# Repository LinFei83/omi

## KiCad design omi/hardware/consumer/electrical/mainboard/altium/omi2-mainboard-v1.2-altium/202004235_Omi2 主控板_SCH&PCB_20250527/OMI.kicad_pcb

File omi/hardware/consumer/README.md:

# Omi Consumer — 开源硬件

Omi Consumer 的完整硬件设计文件，全球领先的开源 AI 可穿戴设备。

采用 MIT 许可证（见 [LICENSE](LICENSE)）。

## 目录说明

### 电气（`electrical/`）
- **主板**（nRF5340 + nRF7002）：Altium 源文件、Gerber、原理图（v1.2）
- **充电板**：Altium 源文件、Gerber、原理图（v1.0）
- **FPC（柔性 PCB）**：Altium 源文件、Gerber、原理图（v1.0）

### 物料清单（`bom/`）
- 88 个元器件，含制造商料号（MPN）
- 提供 CSV 与 XLSX 格式

### 机械（`mechanical/`）
- 整机 + 充电器的完整 STEP 装配体
- 按工艺分类的零件：
  - **CNC**：铝外壳（Case A、Case B）、铜质触摸针
  - **注塑**：包覆/外壳（PC+ABS）
  - **硅胶**：内部衬垫（50A/80A 邵氏硬度）
  - **SLA**：框架、导光件、充电器外壳、增强板
- 二维工程图（PDF）

### 装配（`assembly/`）
- 爆炸图照片
- 元器件识别照片
- 带材料标注的参考图

### 包装（`packaging/`）
- 三维 CAD：泡棉内衬、外壳、钣金、完整装配
- 包装图纸与参考照片

## 技术规格

| 部件 | 规格 |
|-----------|---------------|
| 处理器 | nRF5340 双核 Bluetooth LE SoC |
| Wi-Fi | nRF7002 Wi-Fi 6 芯片 |
| 音频 | 2× TDK T5838 顶出音孔 PDM 麦克风 |
| 存储 | CSNP4GCR01 4Gbit NAND Flash |
| IMU | LSM6DS3TR-C 六轴加速度计/陀螺仪 |
| 电池 | 3.7V 150mAh 锂聚合物（定制，D16×H6.1mm） |
| 充电 | BQ25101 锂离子充电 IC、磁吸弹簧针 |
| 马达 | 3V 振动马达（D5.0×H2.5mm） |

## 固件

固件已开源，位于 [`omi/firmware/`](../../firmware/)。基于 Zephyr RTOS 与 nRF Connect SDK 构建。

## 快速上手

1. **制作一台**：用 Gerber 订购 PCB，用 BOM 采购物料，用 STEP 文件加工外壳。
2. **修改设计**：打开 Altium 源文件定制电路，或编辑 STEP 文件重新设计外壳。
3. **烧录固件**：参阅 [固件指南](https://docs.omi.me/doc/developer/firmware/Compile_firmware)。
4. **文档**：访问 [docs.omi.me](https://docs.omi.me/doc/hardware/consumer) 获取详细说明。

## 文件校验和（SHA-256）

克隆后可用下列校验和核对文件完整性。

```
sha256sum -c checksums.sha256
```

### 电气

| 文件 | SHA-256 |
|------|---------|
| `electrical/mainboard/altium/omi2-mainboard-v1.2-altium.zip` | `025c79effcebaa63de9a4adbf59cfb15b5adfe8f3d61d4c21d268320acf5c133` |
| `electrical/mainboard/gerbers/omi2-mainboard-v1.2-gerbers.zip` | `54e126a1aa4e3174eed50e099c7b930646abad261b7f73421ca1526d39dcee49` |
| `electrical/mainboard/gerbers/omi-gerber-files-main-pcb.zip` | `b2c00ffe2e2483daa9871c45a98f38f49896cbc6b4022a4bbbbffe28217259b3` |
| `electrical/mainboard/schematic.pdf` | `0c09fc65f7c191f6d1ec03932042f78a56688b21bb57b9810204640d6e5f527a` |
| `electrical/charger-board/altium/omi2-charger-v1.0-altium.zip` | `7b15cb87102f177e3feaaeaa8315e3f75bd3790b0cf0c68b0caa763b25ac049c` |
| `electrical/charger-board/gerbers/omi2-charger-v1.0-gerbers.zip` | `e7227b24c951c77fd9a1db11d1249fdf2f6db26cf416fa2ef0cf1816f12c4169` |
| `electrical/charger-board/schematic.pdf` | `282e1c469a0cc73f349fbe4fe050f6e1fdc2a86c1dee61c175a50bb6f247a8ad` |
| `electrical/fpc-board/altium/omi2-fpc-v1.0-altium.zip` | `5f30a4a8ef9d21ca5010f039e791a7845486af58db85bce77637518b146a610b` |
| `electrical/fpc-board/gerbers/omi2-fpc-v1.0-gerbers.zip` | `5a8d56466101ef77fd83dc5bd6016d56542443a865142d23864b07aac712ab2b` |
| `electrical/fpc-board/schematic.pdf` | `31d5c900f54dc586440c8d29093e501bde532c45db455b96ac7c552af102919d` |

### 物料清单（BOM）

| 文件 | SHA-256 |
|------|---------|
| `bom/omi-bom.csv` | `01b27487469ddb8ff7b59258959277e3976d6a150b120a643943505c8f892256` |
| `bom/omi-bom.xlsx` | `1445b549f72a37939be9a38401404e8da7ed45a2029204739dac2733b038987b` |
| `bom/omi-bom-original.xlsx` | `a8744d573bc02b62952e164776f72f30ee7929874666da7b452fbc5e8dde6764` |

### 机械

| 文件 | SHA-256 |
|------|---------|
| `mechanical/assemblies/omi-device-charger-assembly.step` | `d7df1b004e159365b69ef57995a21f49e17dbe18d863b359ef611c6f84e473d1` |
| `mechanical/parts/cnc/case-a.step` | `6a23a0693e3d0e0c3068474cb46931f32e7850d6e22266a902060762f165eb1b` |
| `mechanical/parts/cnc/case-b.step` | `ddeba686dd58d06fc5f3b7934e32dd6d720d037b2a4c1828ee44973795fb7a11` |
| `mechanical/parts/cnc/cnc-brass-copper-zinc-polished.zip` | `d19352e101c9c4bb35c6ccba0e71500f06a0023629ec3a303e3cb3ec4a8192bd` |
| `mechanical/parts/cnc/touchpin-1.step` | `8b9941c24fac07849c3b521528be928ec9fcf8f4f7446e2ea78f02263595e4d0` |
| `mechanical/parts/cnc/touchpin-1-v2.step` | `b26275c3c9857e23c46e0ff133d78fd6c8d8b6d4c82b9c0ef77608e720df142a` |
| `mechanical/parts/cnc/touchpin-2.step` | `260945fac51f3c291ced064b37615027997412f226171bc0815a3425d03e4062` |
| `mechanical/parts/cnc/touchpin-2-v2.step` | `7ac7843fc1616f044c74a0b36d6227394d9abb75b93552982b2965906a684471` |
| `mechanical/parts/injection-molding/wrapper.step` | `4a0c2e9494f973fd6e37deea6c30ded2b52af40364d6e357b15f69722eb4cac8` |
| `mechanical/parts/injection-molding/wrapper-drawing.pdf` | `333f625787012c8eb50a4e3f02a31ef9775dd306811b8f620f5891127021413b` |
| `mechanical/parts/silicone/pad.step` | `e47a7ac6076ca5f99ef911499ea609f04d7efe2fb0d346827ed44e172f3f457b` |
| `mechanical/parts/silicone/pad-drawing.pdf` | `714b057e4f0b508212b27c9fcb55bf80e428468fca3fb14ce970fbdf4ac9b815` |
| `mechanical/parts/sla/charger-case-a-ceramic.step` | `9d0fea420fd38bbe7cfb325e5a3b770150ed9efd02239240b8c14abc075f0ebc` |
| `mechanical/parts/sla/charger-case-b-ceramic.step` | `64296a2503a0b70ac032f7f511de47a7274e6af856bb19faef06a2a72104ce67` |
| `mechanical/parts/sla/enhance-plate-black.step` | `e3c0fb9b6a44966e969fc66fe0ce1a2dc0ac410bb00a3932fdfec307d214c7b6` |
| `mechanical/parts/sla/frame-white-translucent.step` | `a0d96a3dcf0e3b7f85885ee5876ddfd58ce187faea3bd3c10ea4a8f5339b0e86` |
| `mechanical/parts/sla/led-guide-white-translucent.step` | `40f1e31e55e18c5f6df762c69b6b705b651f534851b4defb9bf2ef17e5739bfa` |
| `mechanical/parts/sla/pad-ppt-grey.step` | `1df8786beef2a028c1576c3715eb84aef701804750d9ad90eccee1e989fce6ef` |
| `mechanical/parts/sla/touchpin-2-sla-test.step` | `260945fac51f3c291ced064b37615027997412f226171bc0815a3425d03e4062` |
| `mechanical/drawings/omi-2d-drawings.pdf` | `3eb768218947591cea0ae115219fddd1ae40cc9df332d935681289bb778e8861` |
| `mechanical/drawings/manufacturing-specifications.png` | `13ebd6b23de37919f457b96734538ff36be70ec7d6d5f1e94d7a9826393641fb` |

### 包装

| 文件 | SHA-256 |
|------|---------|
| `packaging/cad/packaging-full-assembly.step` | `95298ba059e96c83456d7396db0f50328eaa3931776e65ccbc60e1698b4fa2e4` |
| `packaging/cad/case-packaging.step` | `cd9e71389791b07a10fb84378a1437f069d26292cc4a977ef2fb76296c7ba28d` |
| `packaging/cad/sheet-metal-packaging.step` | `53259fb0dc6f3a382c1ef16fce84c39a410fb7c9486a35b23282382ea4abb1cd` |
| `packaging/cad/foam/foam-assembly.step` | `06ea31b64fc4ab1a18713a98984cb4200caba8c115ee40ff4204a0fe293d8b19` |
| `packaging/cad/foam/foam-bottom.step` | `7c86f3eca98b3a08b582023cf71148322247ecba5e6482e962646e0d80a5bf0d` |
| `packaging/cad/foam/foam-circle.step` | `d0152f117c1f1968c75fb126f8eb92022194266e44e93af73d75c061aaf38f71` |
| `packaging/cad/foam/foam-top.step` | `89df594615bb795ad6e67a9053b61f468d3617c7edee994ee78692c1e632e5fe` |
| `packaging/cad/foam/foam-packaging.step` | `649380aae5dc56b151604301cd7e0c8223e6055c4f8814643e3c49b76fd06c9a` |
| `packaging/cad/foam/foam-drawing.pdf` | `6b1686aa8c1d89c2dc5d511c2abb55b1f456d508b9485d78f037599c10ac2671` |
| `packaging/package-drawing.pdf` | `f9b64171b32a1c432ecd3949f5fc51a28b339b52336c23ef70b2f9e335c173f9` |

### 装配照片

| 文件 | SHA-256 |
|------|---------|
| `assembly/photos/components-disassembled.jpg` | `880e774b49f56a8ec7bf4f4075483f5c0bcf7c0e39962d874d54deb0428b5b71` |
| `assembly/photos/materials-labelled-exploded-view.jpg` | `0cb3e22f08dceaa5cce9c569510985251c2b6c580718ad8d2559987019c2fd00` |
| `assembly/photos/materials-labelled.jpg` | `7857e7b6f7e1686899dd51ec9d11196905ff1f539f09aff08ae2b724904a9555` |
| `assembly/photos/outer-aluminium-covers.jpg` | `0ce99ecfffba3b11a91e754c90c9f4b8c1a14c779b1124cbe6c8b6a69ce71ab1` |

### 包装照片

| 文件 | SHA-256 |
|------|---------|
| `packaging/photos/disassembly-exploded-view.png` | `bfc5a0fa7ed8997aa882cefcff1b7a750578aa6e323e63b720de7ea64d3d54a4` |
| `packaging/photos/package-overview.png` | `2556dd78a18397aa58ed8cb27edd48de5536ce08168a2db371de3e7564f476ad` |
| `packaging/photos/package-render.png` | `2556dd78a18397aa58ed8cb27edd48de5536ce08168a2db371de3e7564f476ad` |
| `packaging/photos/packaging-1.jpg` | `6bf951f71209730e5e031fd28e1e7dc192c86e2b3a5cfdaacd80d8efff77ae38` |
| `packaging/photos/packaging-2.jpg` | `4104233eb7f29c6560d2bfcfbc60bfeea79bc3a1877fb97c0fd19447a350feb1` |
| `packaging/photos/packaging-3.jpg` | `c3ab8314c2465191edaf23849f7da921058b2773add5b372a2891126229362fd` |
| `packaging/photos/packaging-4.jpg` | `6821e45eefc5d4557b88b6282887abebaa9658a7b9f12883f3ca42f4b9e5d2c8` |
| `packaging/photos/packaging-5.jpg` | `f1cd74ab68fbfde7d149bd36ec4f3a5186740af792470c9f2417c561e02404ab` |
| `packaging/photos/packaging-6.jpg` | `a2288a15cb8e9ac8dfc074fed6a6e61a060ff09cecffc6939a92948bfa8dccb5` |
| `packaging/photos/packaging-7.jpg` | `5d0ceae15ed4191c43319c450d89e9a3fcd9ae35db05f605336dd9c8e6d1ca70` |

## 有疑问？

- [GitHub Issues](https://github.com/BasedHardware/omi/issues)：缺陷与功能建议
- [Discord](https://discord.gg/omi)：社区讨论

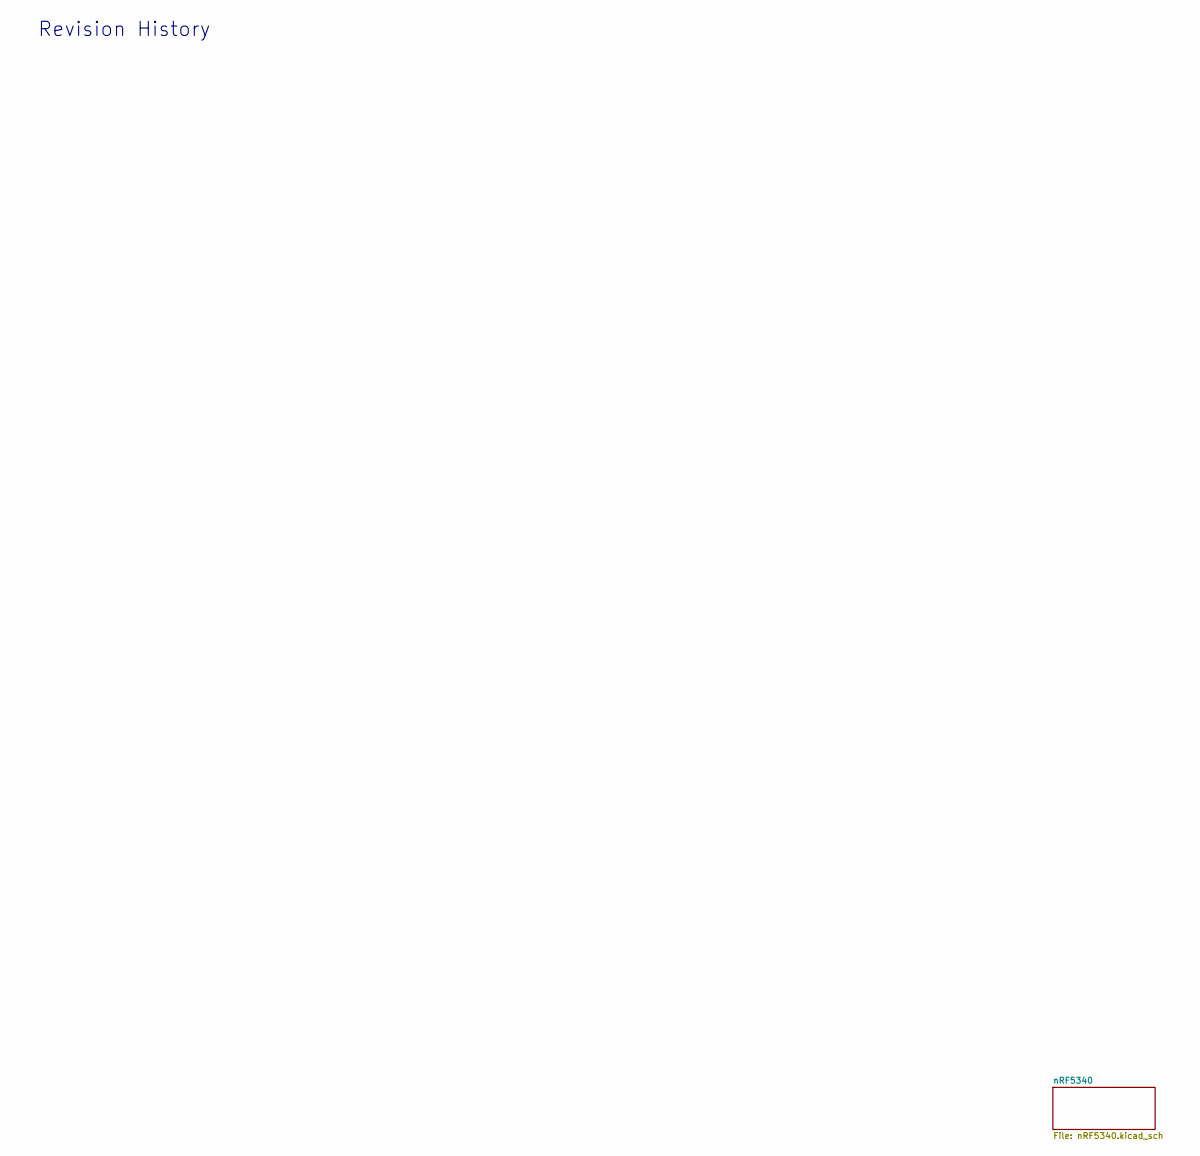
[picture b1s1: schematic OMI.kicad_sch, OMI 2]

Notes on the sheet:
Revision History

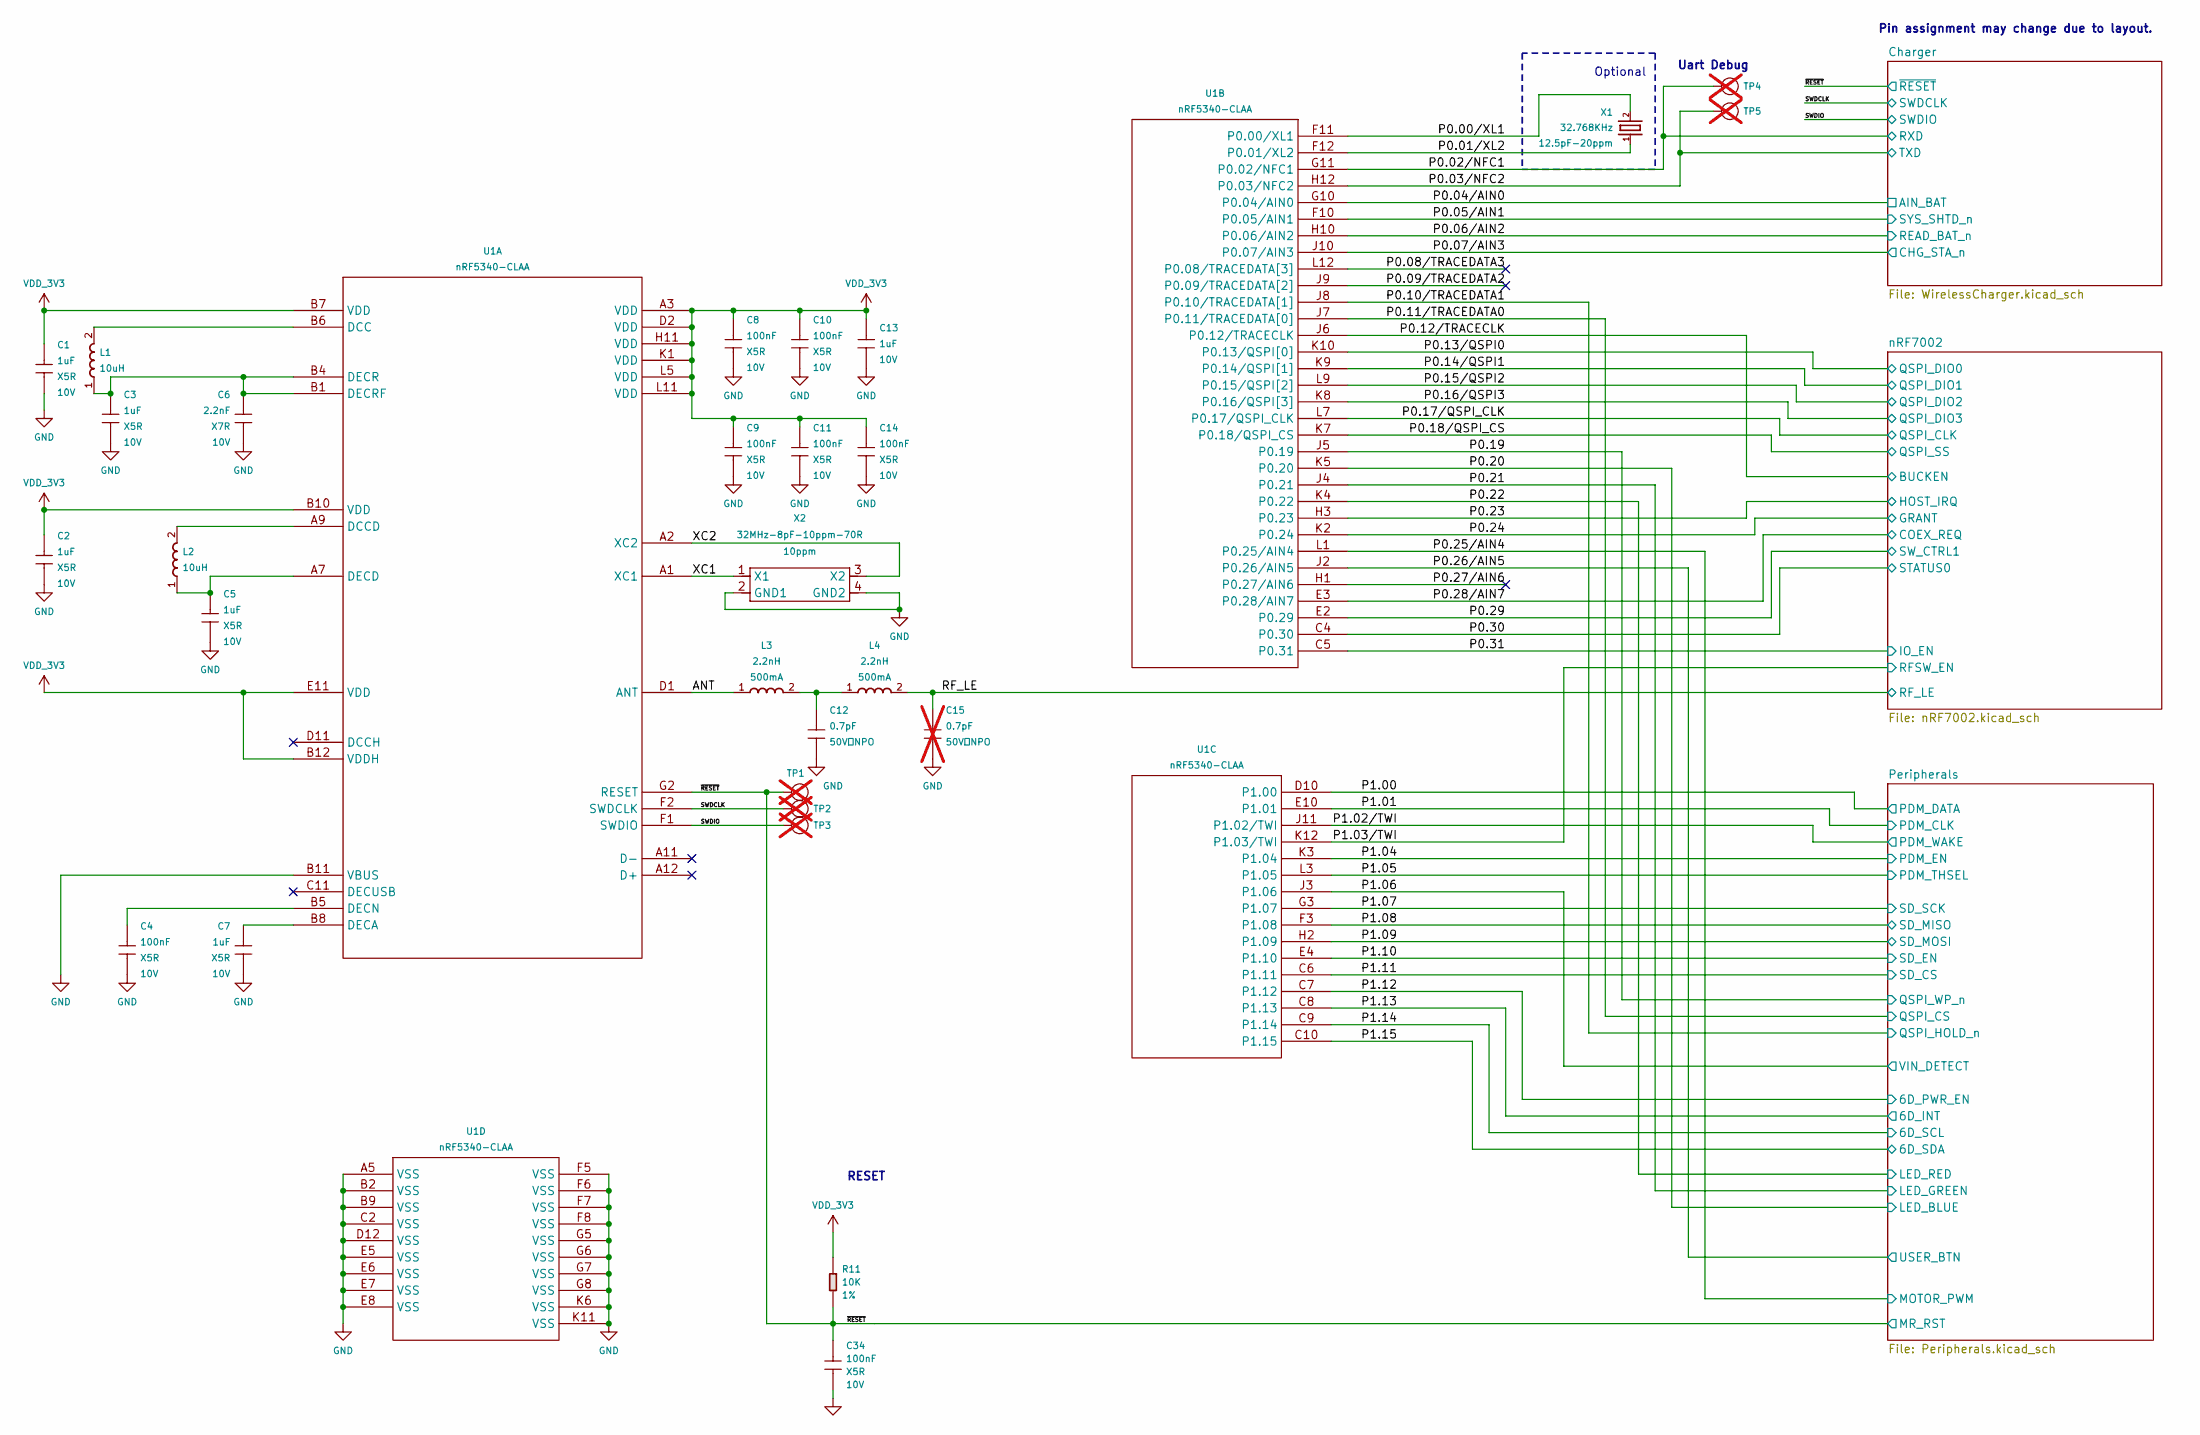
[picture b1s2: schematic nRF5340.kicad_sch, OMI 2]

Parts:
C1, C2, C3, C5, C7, C13: 1uF; C0201; Voltage Rating 10V; MPN GRM033R61A105ME44D
C4, C8, C9, C10, C11, C14, C34: 100nF; C0201; Voltage Rating 10V; MPN CC0201KRX5R6BB104
C6: 2.2nF; C0201; Voltage Rating 10V; MPN CC0201KRX7R6BB222
C12: 0.7pF; C0201; MPN CC0201BRNPO9BNR70
C15: 0.7pF; C0201; MPN CC0201BRNPO9BNR70; not fitted
L1, L2: 10uH; L0603; MPN MWSD1608FE100KT
L3, L4: 2.2nH; L0201; Rating 500mA; MPN CHQ0603T-2N2B-HU
R11: 10K; R0201; Power Rating 1%; MPN RC0201FR-0710KL
TP1, TP2, TP3, TP4, TP5: Test Point; TP-1X0.9MM; Part Type Test Point; not fitted
U1: nRF5340-CLAA; WLCSP94-0.35-4.39X3.994X0.447MM; MPN nRF5340-CLAA
X1: 32.768KHz; X2-SMD-1.6X1.0MM; Rating 12.5pF-20ppm; MPN DST1610A
X2: 32MHz-8pF-10ppm-70R; X4-SMD-1.6X1.2MM; Rating 10ppm; MPN 1S32000049

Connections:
/nRF5340/ANT: L3.1, U1.D1 (ANT)
/nRF5340/P0.00/XL1: U1.F11 (P0.00/XL1), X1.2
/nRF5340/P0.01/XL2: U1.F12 (P0.01/XL2), X1.1
/nRF5340/P0.02/NFC1: TP4.1 (T), U1.G11 (P0.02/NFC1); also elsewhere on the board
/nRF5340/P0.03/NFC2: TP5.1 (T), U1.H12 (P0.03/NFC2); also elsewhere on the board
/nRF5340/P0.04/AIN0: U1.G10 (P0.04/AIN0); also elsewhere on the board
/nRF5340/P0.05/AIN1: U1.F10 (P0.05/AIN1); also elsewhere on the board
/nRF5340/P0.06/AIN2: U1.H10 (P0.06/AIN2); also elsewhere on the board
/nRF5340/P0.07/AIN3: U1.J10 (P0.07/AIN3); also elsewhere on the board
/nRF5340/P0.08/TRACEDATA3: U1.L12 (P0.08/TRACEDATA[3])
/nRF5340/P0.09/TRACEDATA2: U1.J9 (P0.09/TRACEDATA[2])
/nRF5340/P0.10/TRACEDATA1: U1.J8 (P0.10/TRACEDATA[1]); also elsewhere on the board
/nRF5340/P0.11/TRACEDATA0: U1.J7 (P0.11/TRACEDATA[0]); also elsewhere on the board
/nRF5340/P0.12/TRACECLK: U1.J6 (P0.12/TRACECLK); also elsewhere on the board
/nRF5340/P0.13/QSPI0: U1.K10 (P0.13/QSPI[0]); also elsewhere on the board
/nRF5340/P0.14/QSPI1: U1.K9 (P0.14/QSPI[1]); also elsewhere on the board
/nRF5340/P0.15/QSPI2: U1.L9 (P0.15/QSPI[2]); also elsewhere on the board
/nRF5340/P0.16/QSPI3: U1.K8 (P0.16/QSPI[3]); also elsewhere on the board
/nRF5340/P0.17/QSPI_CLK: U1.L7 (P0.17/QSPI_CLK); also elsewhere on the board
/nRF5340/P0.18/QSPI_CS: U1.K7 (P0.18/QSPI_CS); also elsewhere on the board
/nRF5340/P0.19: U1.J5 (P0.19); also elsewhere on the board
/nRF5340/P0.20: U1.K5 (P0.20); also elsewhere on the board
/nRF5340/P0.21: U1.J4 (P0.21); also elsewhere on the board
/nRF5340/P0.22: U1.K4 (P0.22); also elsewhere on the board
/nRF5340/P0.23: U1.H3 (P0.23); also elsewhere on the board
/nRF5340/P0.24: U1.K2 (P0.24); also elsewhere on the board
/nRF5340/P0.25/AIN4: U1.L1 (P0.25/AIN4); also elsewhere on the board
/nRF5340/P0.26/AIN5: U1.J2 (P0.26/AIN5); also elsewhere on the board
/nRF5340/P0.27/AIN6: U1.H1 (P0.27/AIN6)
/nRF5340/P0.28/AIN7: U1.E3 (P0.28/AIN7); also elsewhere on the board
/nRF5340/P0.29: U1.E2 (P0.29); also elsewhere on the board
/nRF5340/P0.30: U1.C4 (P0.30); also elsewhere on the board
/nRF5340/P0.31: U1.C5 (P0.31); also elsewhere on the board
/nRF5340/P1.00: U1.D10 (P1.00); also elsewhere on the board
/nRF5340/P1.01: U1.E10 (P1.01); also elsewhere on the board
/nRF5340/P1.02/TWI: U1.J11 (P1.02/TWI); also elsewhere on the board
/nRF5340/P1.03/TWI: U1.K12 (P1.03/TWI); also elsewhere on the board
/nRF5340/P1.04: U1.K3 (P1.04); also elsewhere on the board
/nRF5340/P1.05: U1.L3 (P1.05); also elsewhere on the board
/nRF5340/P1.06: U1.J3 (P1.06); also elsewhere on the board
/nRF5340/P1.07: U1.G3 (P1.07); also elsewhere on the board
/nRF5340/P1.08: U1.F3 (P1.08); also elsewhere on the board
/nRF5340/P1.09: U1.H2 (P1.09); also elsewhere on the board
/nRF5340/P1.10: U1.E4 (P1.10); also elsewhere on the board
/nRF5340/P1.11: U1.C6 (P1.11); also elsewhere on the board
/nRF5340/P1.12: U1.C7 (P1.12); also elsewhere on the board
/nRF5340/P1.13: U1.C8 (P1.13); also elsewhere on the board
/nRF5340/P1.14: U1.C9 (P1.14); also elsewhere on the board
/nRF5340/P1.15: U1.C10 (P1.15); also elsewhere on the board
/nRF5340/RF_LE: C15.1, L4.2; also elsewhere on the board
/nRF5340/SWDCLK: TP2.1 (T), U1.F2 (SWDCLK); also elsewhere on the board
/nRF5340/SWDIO: TP3.1 (T), U1.F1 (SWDIO); also elsewhere on the board
/nRF5340/XC1: U1.A1 (XC1), X2.1 (X1)
/nRF5340/XC2: U1.A2 (XC2), X2.3 (X2)
/nRF5340/~RESET: C34.1, R11.2, TP1.1 (T), U1.G2 (RESET); also elsewhere on the board
GND: C1.2, C2.2, C3.2, C4.2, C5.2, C6.2, C7.2, C8.2, C9.2, C10.2, C11.2, C12.2, C13.1, C14.2, C15.2, C34.2, U1.A5 (VSS), U1.B2 (VSS), U1.B9 (VSS), U1.B11 (VBUS), U1.C2 (VSS), U1.D12 (VSS), U1.E5 (VSS), U1.E6 (VSS), U1.E7 (VSS), U1.E8 (VSS), U1.F5 (VSS), U1.F6 (VSS), U1.F7 (VSS), U1.F8 (VSS), U1.G5 (VSS), U1.G6 (VSS), U1.G7 (VSS), U1.G8 (VSS), U1.K6 (VSS), U1.K11 (VSS), X2.2 (GND1), X2.4 (GND2); also elsewhere on the board
unnamed: C12.1, L3.2, L4.1
unnamed: L1.2, U1.B6 (DCC)
unnamed: L2.2, U1.A9 (DCCD)
unnamed: C7.1, U1.B8 (DECA)
unnamed: C5.1, L2.1, U1.A7 (DECD)
unnamed: C4.1, U1.B5 (DECN)
unnamed: C3.1, C6.1, L1.1, U1.B1 (DECRF), U1.B4 (DECR)
VDD_3V3: C1.1, C2.1, C8.1, C9.1, C10.1, C11.1, C13.2, C14.1, R11.1, U1.A3 (VDD), U1.B7 (VDD), U1.B10 (VDD), U1.B12 (VDDH), U1.D2 (VDD), U1.E11 (VDD), U1.H11 (VDD), U1.K1 (VDD), U1.L5 (VDD), U1.L11 (VDD); also elsewhere on the board

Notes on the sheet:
Uart Debug
RESET
Pin assignment may change due to layout.
Optional

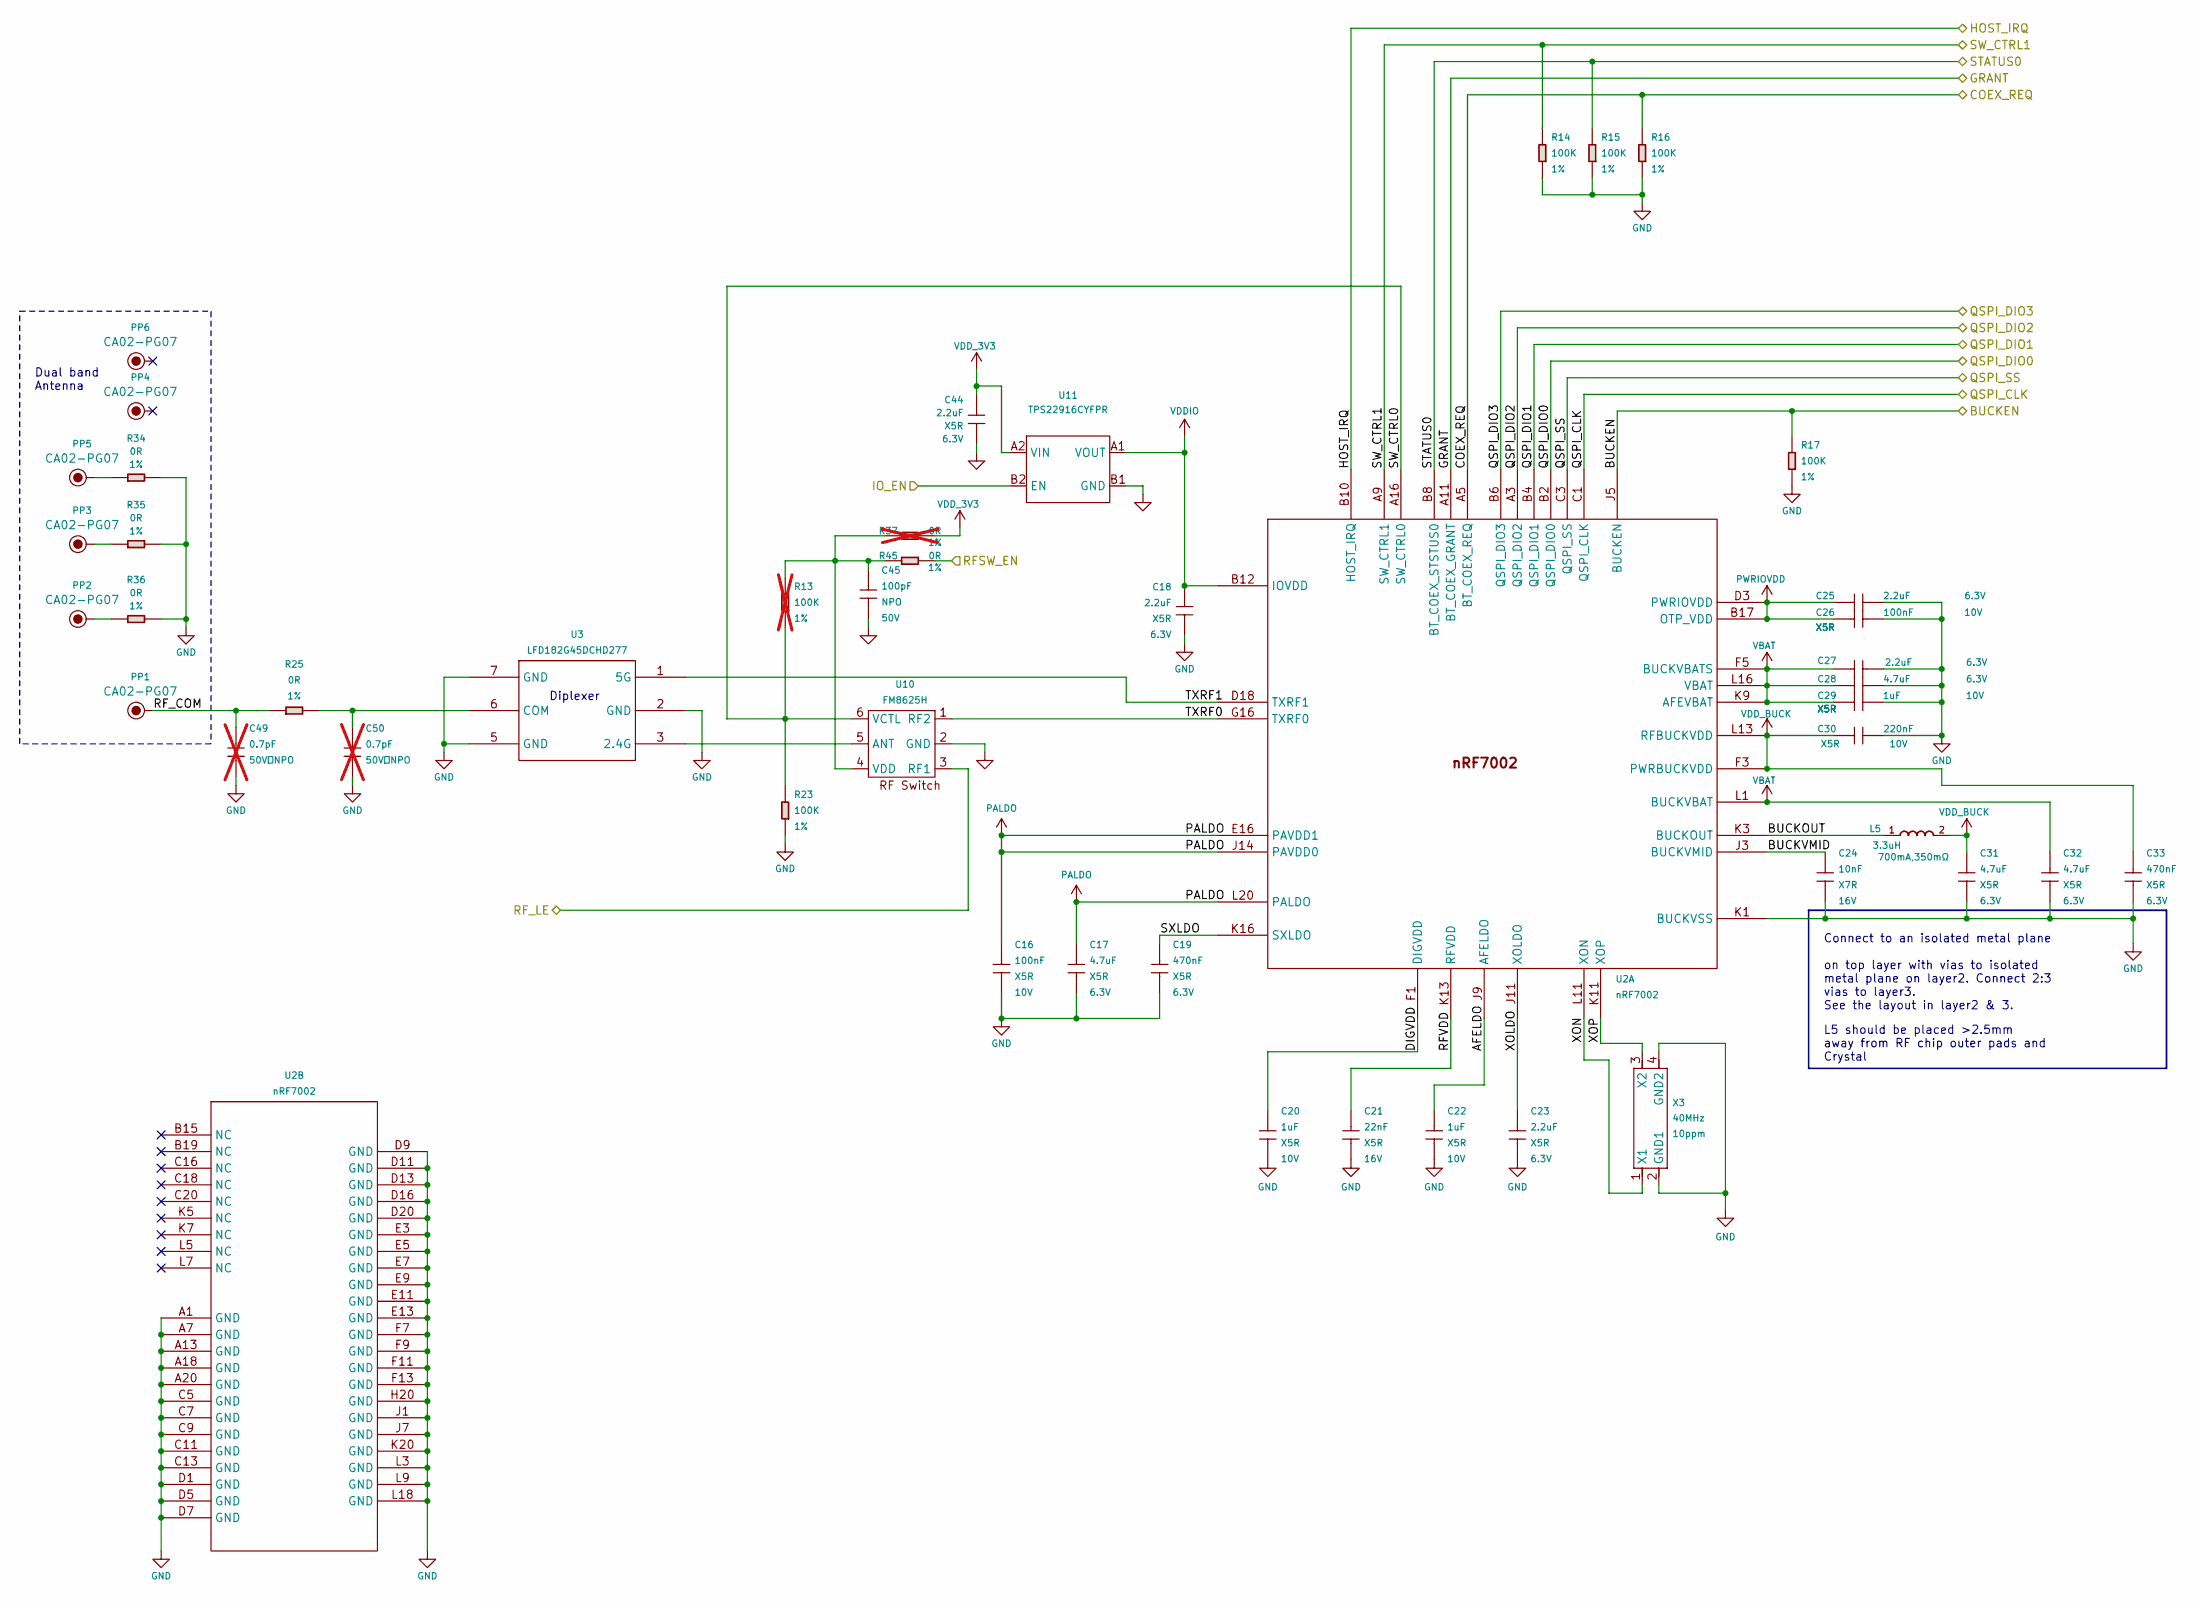
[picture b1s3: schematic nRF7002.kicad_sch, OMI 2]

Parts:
C16, C26: 100nF; C0201; Voltage Rating 10V; MPN CC0201KRX5R6BB104
C17, C28, C31, C32: 4.7uF; C0201; Voltage Rating 6.3V; MPN GRM035R60J475ME15D
C18, C23, C25, C27, C44: 2.2uF; C0201; Voltage Rating 6.3V; MPN 0201X225M6R3NT
C19, C33: 470nF; C0201; Voltage Rating 6.3V; MPN CC0201KRX5R5BB474
C20, C22, C29: 1uF; C0201; Voltage Rating 10V; MPN GRM033R61A105ME44D
C21: 22nF; C0201; Voltage Rating 16V; MPN GRM033R61C223KE84D
C24: 10nF; C0201; Voltage Rating 16V; MPN CC0201KRX7R7BB103
C30: 220nF; C0201; Voltage Rating 10V; MPN CC0201KRX5R6BB224
C45: 100pF; C0201; Voltage Rating 50V; MPN CC0201JRNPO9BN101
C49, C50: 0.7pF; C0201; MPN CC0201BRNPO9BNR70; not fitted
L5: 3.3uH; L0603; Rating 700mA,350mΩ; MPN LQM18PN3R3MFRL
PP1, PP2, PP3, PP4, PP5, PP6: CA02-PG07; POGOPIN-1.4MM-ROUND; MPN CA02-PG07
R13: 100K; R0201; Power Rating 1%; MPN RC0201FR-07100KL; not fitted
R14, R15, R16, R17, R23: 100K; R0201; Power Rating 1%; MPN RC0201FR-07100KL
R25, R34, R35, R36, R45: 0R; R0201; Power Rating 1%; MPN RC0201FR-070RL
R37: 0R; R0201; Power Rating 1%; MPN RC0201FR-070RL; not fitted
U2: nRF7002; nRF7002_WLCSP_R2; MPN nRF7002-CEAA-R7
U3: LFD182G45DCHD277; CAF-50P160X80-6N; MPN LFD182G45DCHD277
U10: FM8625H; DFN6-0.4-1.1X0.7X0.45MM; MPN FM8625H
U11: TPS22916CYFPR; WLCSP4-0.4-0.77X0.77X0.33MM; MPN TPS22916CYFPR
X3: 40MHz; X4-SMD-1.6X1.2MM; Rating 10ppm; MPN CJ17-400001010B20

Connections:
/nRF5340/P0.12/TRACECLK: R17.2, U2.J5 (BUCKEN); also elsewhere on the board
/nRF5340/P0.13/QSPI0: U2.B2 (QSPI_DIO0); also elsewhere on the board
/nRF5340/P0.14/QSPI1: U2.B4 (QSPI_DIO1); also elsewhere on the board
/nRF5340/P0.15/QSPI2: U2.A3 (QSPI_DIO2); also elsewhere on the board
/nRF5340/P0.16/QSPI3: U2.B6 (QSPI_DIO3); also elsewhere on the board
/nRF5340/P0.17/QSPI_CLK: U2.C1 (QSPI_CLK); also elsewhere on the board
/nRF5340/P0.18/QSPI_CS: U2.C3 (QSPI_SS); also elsewhere on the board
/nRF5340/P0.23: U2.B10 (HOST_IRQ); also elsewhere on the board
/nRF5340/P0.24: U2.A11 (BT_COEX_GRANT); also elsewhere on the board
/nRF5340/P0.28/AIN7: R16.2, U2.A5 (BT_COEX_REQ); also elsewhere on the board
/nRF5340/P0.29: R14.2, U2.A9 (SW_CTRL1); also elsewhere on the board
/nRF5340/P0.30: R15.2, U2.B8 (BT_COEX_STSTUS0); also elsewhere on the board
/nRF5340/P0.31: U11.B2 (EN); also elsewhere on the board
/nRF5340/P1.03/TWI: R45.2; also elsewhere on the board
/nRF5340/RF_LE: U10.3 (RF1); also elsewhere on the board
/nRF5340/nRF7002/AFELDO: C22.1, U2.J9 (AFELDO)
/nRF5340/nRF7002/BUCKOUT: L5.1, U2.K3 (BUCKOUT)
/nRF5340/nRF7002/BUCKVMID: C24.1, U2.J3 (BUCKVMID)
/nRF5340/nRF7002/DIGVDD: C20.2, U2.F1 (DIGVDD)
/nRF5340/nRF7002/RFVDD: C21.1, U2.K13 (RFVDD)
/nRF5340/nRF7002/RF_COM: C49.1, PP1.1 (T), R25.1
/nRF5340/nRF7002/SW_CTRL0: R13.1, R23.2, U2.A16 (SW_CTRL0), U10.6 (VCTL)
/nRF5340/nRF7002/SXLDO: C19.1, U2.K16 (SXLDO)
/nRF5340/nRF7002/TXRF0: U2.G16 (TXRF0), U10.1 (RF2)
/nRF5340/nRF7002/TXRF1: U2.D18 (TXRF1), U3.1 (5G)
/nRF5340/nRF7002/XOLDO: C23.1, U2.J11 (XOLDO)
/nRF5340/nRF7002/XON: U2.L11 (XON), X3.1 (X1)
/nRF5340/nRF7002/XOP: U2.K11 (XOP), X3.3 (X2)
GND: C16.2, C17.2, C18.2, C19.2, C20.1, C21.2, C22.2, C23.2, C24.2, C25.2, C26.2, C27.2, C28.2, C29.2, C30.2, C31.2, C32.2, C33.2, C44.1, C45.2, C49.2, C50.2, R14.1, R15.1, R16.1, R17.1, R23.1, R34.2, R35.2, R36.2, U2.A1 (GND), U2.A7 (GND), U2.A13 (GND), U2.A18 (GND), U2.A20 (GND), U2.C5 (GND), U2.C7 (GND), U2.C9 (GND), U2.C11 (GND), U2.C13 (GND), U2.D1 (GND), U2.D5 (GND), U2.D7 (GND), U2.D9 (GND), U2.D11 (GND), U2.D13 (GND), U2.D16 (GND), U2.D20 (GND), U2.E3 (GND), U2.E5 (GND), U2.E7 (GND), U2.E9 (GND), U2.E11 (GND), U2.E13 (GND), U2.F7 (GND), U2.F9 (GND), U2.F11 (GND), U2.F13 (GND), U2.H20 (GND), U2.J1 (GND), U2.J7 (GND), U2.K1 (BUCKVSS), U2.K20 (GND), U2.L3 (GND), U2.L9 (GND), U2.L18 (GND), U3.2 (GND), U3.5 (GND), U3.7 (GND), U10.2 (GND), U11.B1 (GND), X3.2 (GND1), X3.4 (GND2); also elsewhere on the board
unnamed: PP2.1 (T), R36.1
unnamed: PP3.1 (T), R35.1
unnamed: PP5.1 (T), R34.1
unnamed: C50.1, R25.2, U3.6 (COM)
unnamed: U3.3 (2.4G), U10.5 (ANT)
unnamed: C45.1, R13.2, R37.1, R45.1, U10.4 (VDD)
PALDO: C16.1, C17.1, U2.E16 (PAVDD1), U2.J14 (PAVDD0), U2.L20 (PALDO)
PWRIOVDD: C25.1, C26.1, U2.B17 (OTP_VDD), U2.D3 (PWRIOVDD)
VBAT: C27.1, C28.1, C29.1, C32.1, U2.F5 (BUCKVBATS), U2.K9 (AFEVBAT), U2.L1 (BUCKVBAT), U2.L16 (VBAT); also elsewhere on the board
VDDIO: C18.1, U2.B12 (IOVDD), U11.A1 (VOUT)
VDD_3V3: C44.2, R37.2, U11.A2 (VIN); also elsewhere on the board
VDD_BUCK: C30.1, C31.1, C33.1, L5.2, U2.F3 (PWRBUCKVDD), U2.L13 (RFBUCKVDD)

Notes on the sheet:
Diplexer
Connect to an isolated metal plane on top layer with vias to isolated metal plane on layer2. Connect 2:3 vias to layer3. See the layout in layer2 & 3.
L5 should be placed >2.5mm away from RF chip outer pads and Crystal
Dual band Antenna

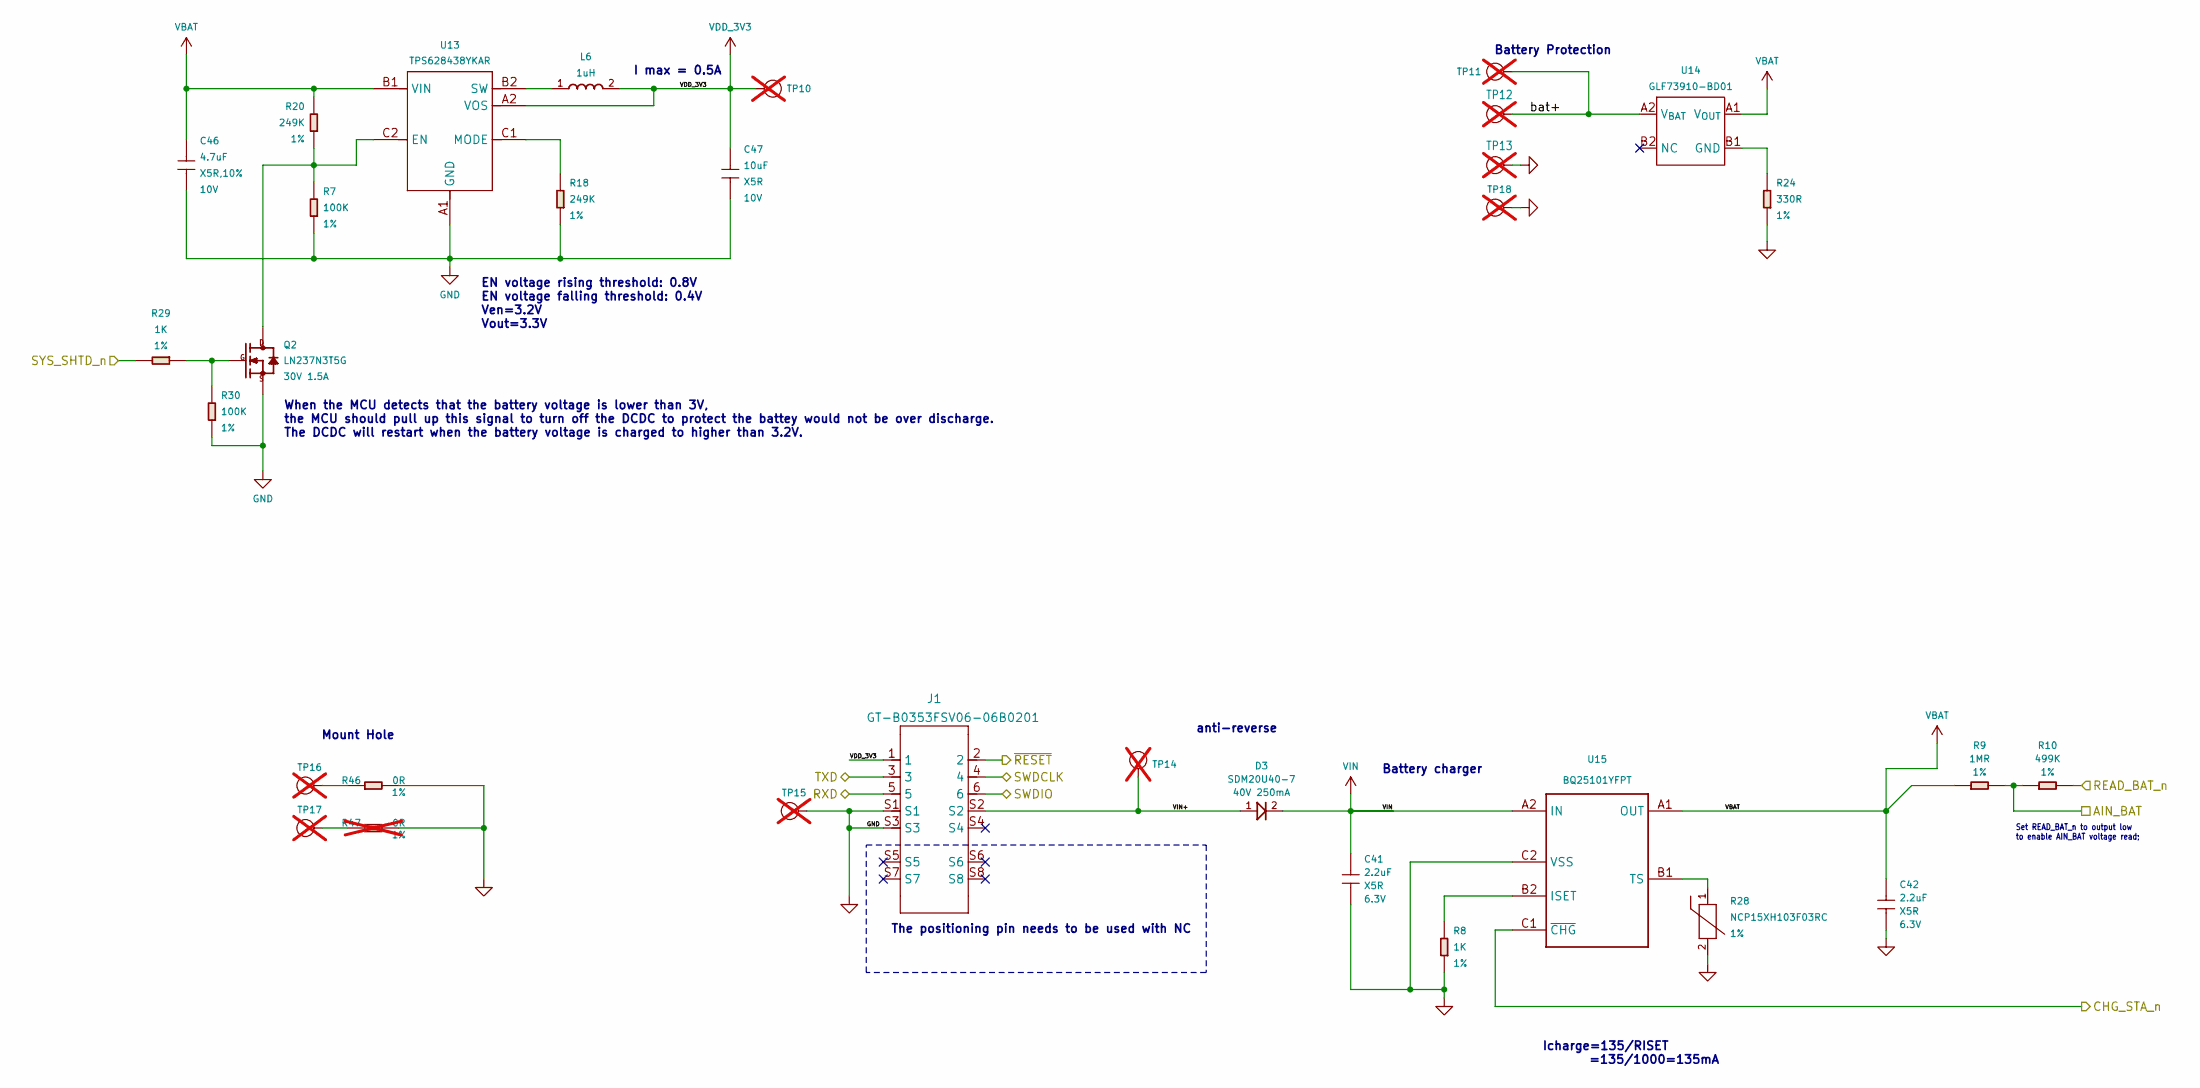
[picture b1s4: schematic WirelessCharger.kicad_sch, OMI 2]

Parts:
C41, C42: 2.2uF; C0201; Voltage Rating 6.3V; MPN 0201X225M6R3NT
C46: 4.7uF; C0402; Voltage Rating 10V; MPN CC0402KRX5R6BB475
C47: 10uF; C0402; Voltage Rating 10V; MPN CC0402MRX5R6BB106
D3: SDM20U40-7; SOD-523; Rating 40V 250mA; MPN SDM20U40-7
J1: GT-B0353FSV06-06B0201; BTB6_0d35_3_16x1_5x0_6mm; MPN GT-B0353FSV06-06B0201
L6: 1uH; L0603; MPN LQM18PN1R0MFRL
Q2: LN237N3T5G; PMOS_1.0X0.6X0.35MM; Rating 30V 1.5A; MPN LN237N3T5G
R7, R30: 100K; R0201; Power Rating 1%; MPN RC0201FR-07100KL
R8, R29: 1K; R0201; Power Rating 1%; MPN RC0201FR-071KL
R9: 1MR; R0201; Power Rating 1%; MPN RC0201FR-071ML
R10: 499K; R0201; Power Rating 1%; MPN RC0201FR-07499KL
R18, R20: 249K; R0201; Power Rating 1%; MPN RC0201FR-07249KL
R24: 330R; R0201; Power Rating 1%; MPN RC0201FR-07330RL
R28: NCP15XH103F03RC; R0402; Power Rating 1%; MPN NCP15XH103F03RC
R46: 0R; R0201; Power Rating 1%; MPN RC0201FR-070RL
R47: 0R; R0201; Power Rating 1%; MPN RC0201FR-070RL; not fitted
TP10, TP11, TP14, TP15, TP18: Test Point; TP-1X0.9MM; Part Type Test Point; not fitted
TP12, TP13: Test Point; TP-1.6X0.8MM; Part Type Test Point; not fitted
TP16, TP17: Test Point; TP-D2_5c1_3mm; Part Type Test Point; not fitted
U13: TPS628438YKAR; BGA6-0.35-0.85X1.2X0.4MM; MPN TPS628438YKAR
U14: GLF73910-BD01; SMD-WLCSP-4; MPN GLF73910-BD01
U15: BQ25101YFPT; DSBGA6-0.4-1.6x0.9x0.5mm; MPN BQ25101YFPT

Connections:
/nRF5340/Charger/VIN+: D3.1, J1.S2, TP14.1 (T)
/nRF5340/Charger/bat+: TP11.1 (T), TP12.1 (T), U14.A2 (V_{BAT})
/nRF5340/P0.02/NFC1: J1.5; also elsewhere on the board
/nRF5340/P0.03/NFC2: J1.3; also elsewhere on the board
/nRF5340/P0.04/AIN0: R9.2, R10.1; also elsewhere on the board
/nRF5340/P0.05/AIN1: R29.2; also elsewhere on the board
/nRF5340/P0.06/AIN2: R10.2; also elsewhere on the board
/nRF5340/P0.07/AIN3: U15.C1 (~CHG); also elsewhere on the board
/nRF5340/SWDCLK: J1.4; also elsewhere on the board
/nRF5340/SWDIO: J1.6; also elsewhere on the board
/nRF5340/~RESET: J1.2; also elsewhere on the board
GND: C41.1, C42.2, C46.2, C47.2, J1.S1, J1.S3, Q2.2 (S), R7.1, R8.1, R18.1, R24.1, R28.2, R30.1, R46.2, R47.2, TP13.1 (T), TP15.1 (T), TP18.1 (T), U13.A1 (GND), U15.C2 (VSS); also elsewhere on the board
unnamed: Q2.3 (D), R7.2, R20.1, U13.C2 (EN)
unnamed: Q2.1 (G), R29.1, R30.2
unnamed: R46.1, TP16.1 (T)
unnamed: R47.1, TP17.1 (T)
unnamed: R18.2, U13.C1 (MODE)
unnamed: L6.1, U13.B2 (SW)
unnamed: R24.2, U14.B1 (GND)
unnamed: R8.2, U15.B2 (ISET)
unnamed: R28.1, U15.B1 (TS)
VBAT: C42.1, C46.1, R9.1, R20.2, U13.B1 (VIN), U14.A1 (V_{OUT}), U15.A1 (OUT); also elsewhere on the board
VDD_3V3: C47.1, J1.1, L6.2, TP10.1 (T), U13.A2 (VOS); also elsewhere on the board
VIN: C41.2, D3.2, U15.A2 (IN); also elsewhere on the board

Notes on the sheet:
Battery Protection
I max = 0.5A
The positioning pin needs to be used with NC
Mount Hole
When the MCU detects that the battery voltage is lower than 3V, the MCU should pull up this signal to turn off the DCDC to protect the battey would not be over discharge. The DCDC will restart when the battery voltage is charged to higher than 3.2V.
Set READ_BAT_n to output low to enable AIN_BAT voltage read;
Battery charger
EN voltage rising threshold: 0.8V EN voltage falling threshold: 0.4V Ven=3.2V Vout=3.3V
Icharge=135/RISET =135/1000=135mA
anti-reverse
